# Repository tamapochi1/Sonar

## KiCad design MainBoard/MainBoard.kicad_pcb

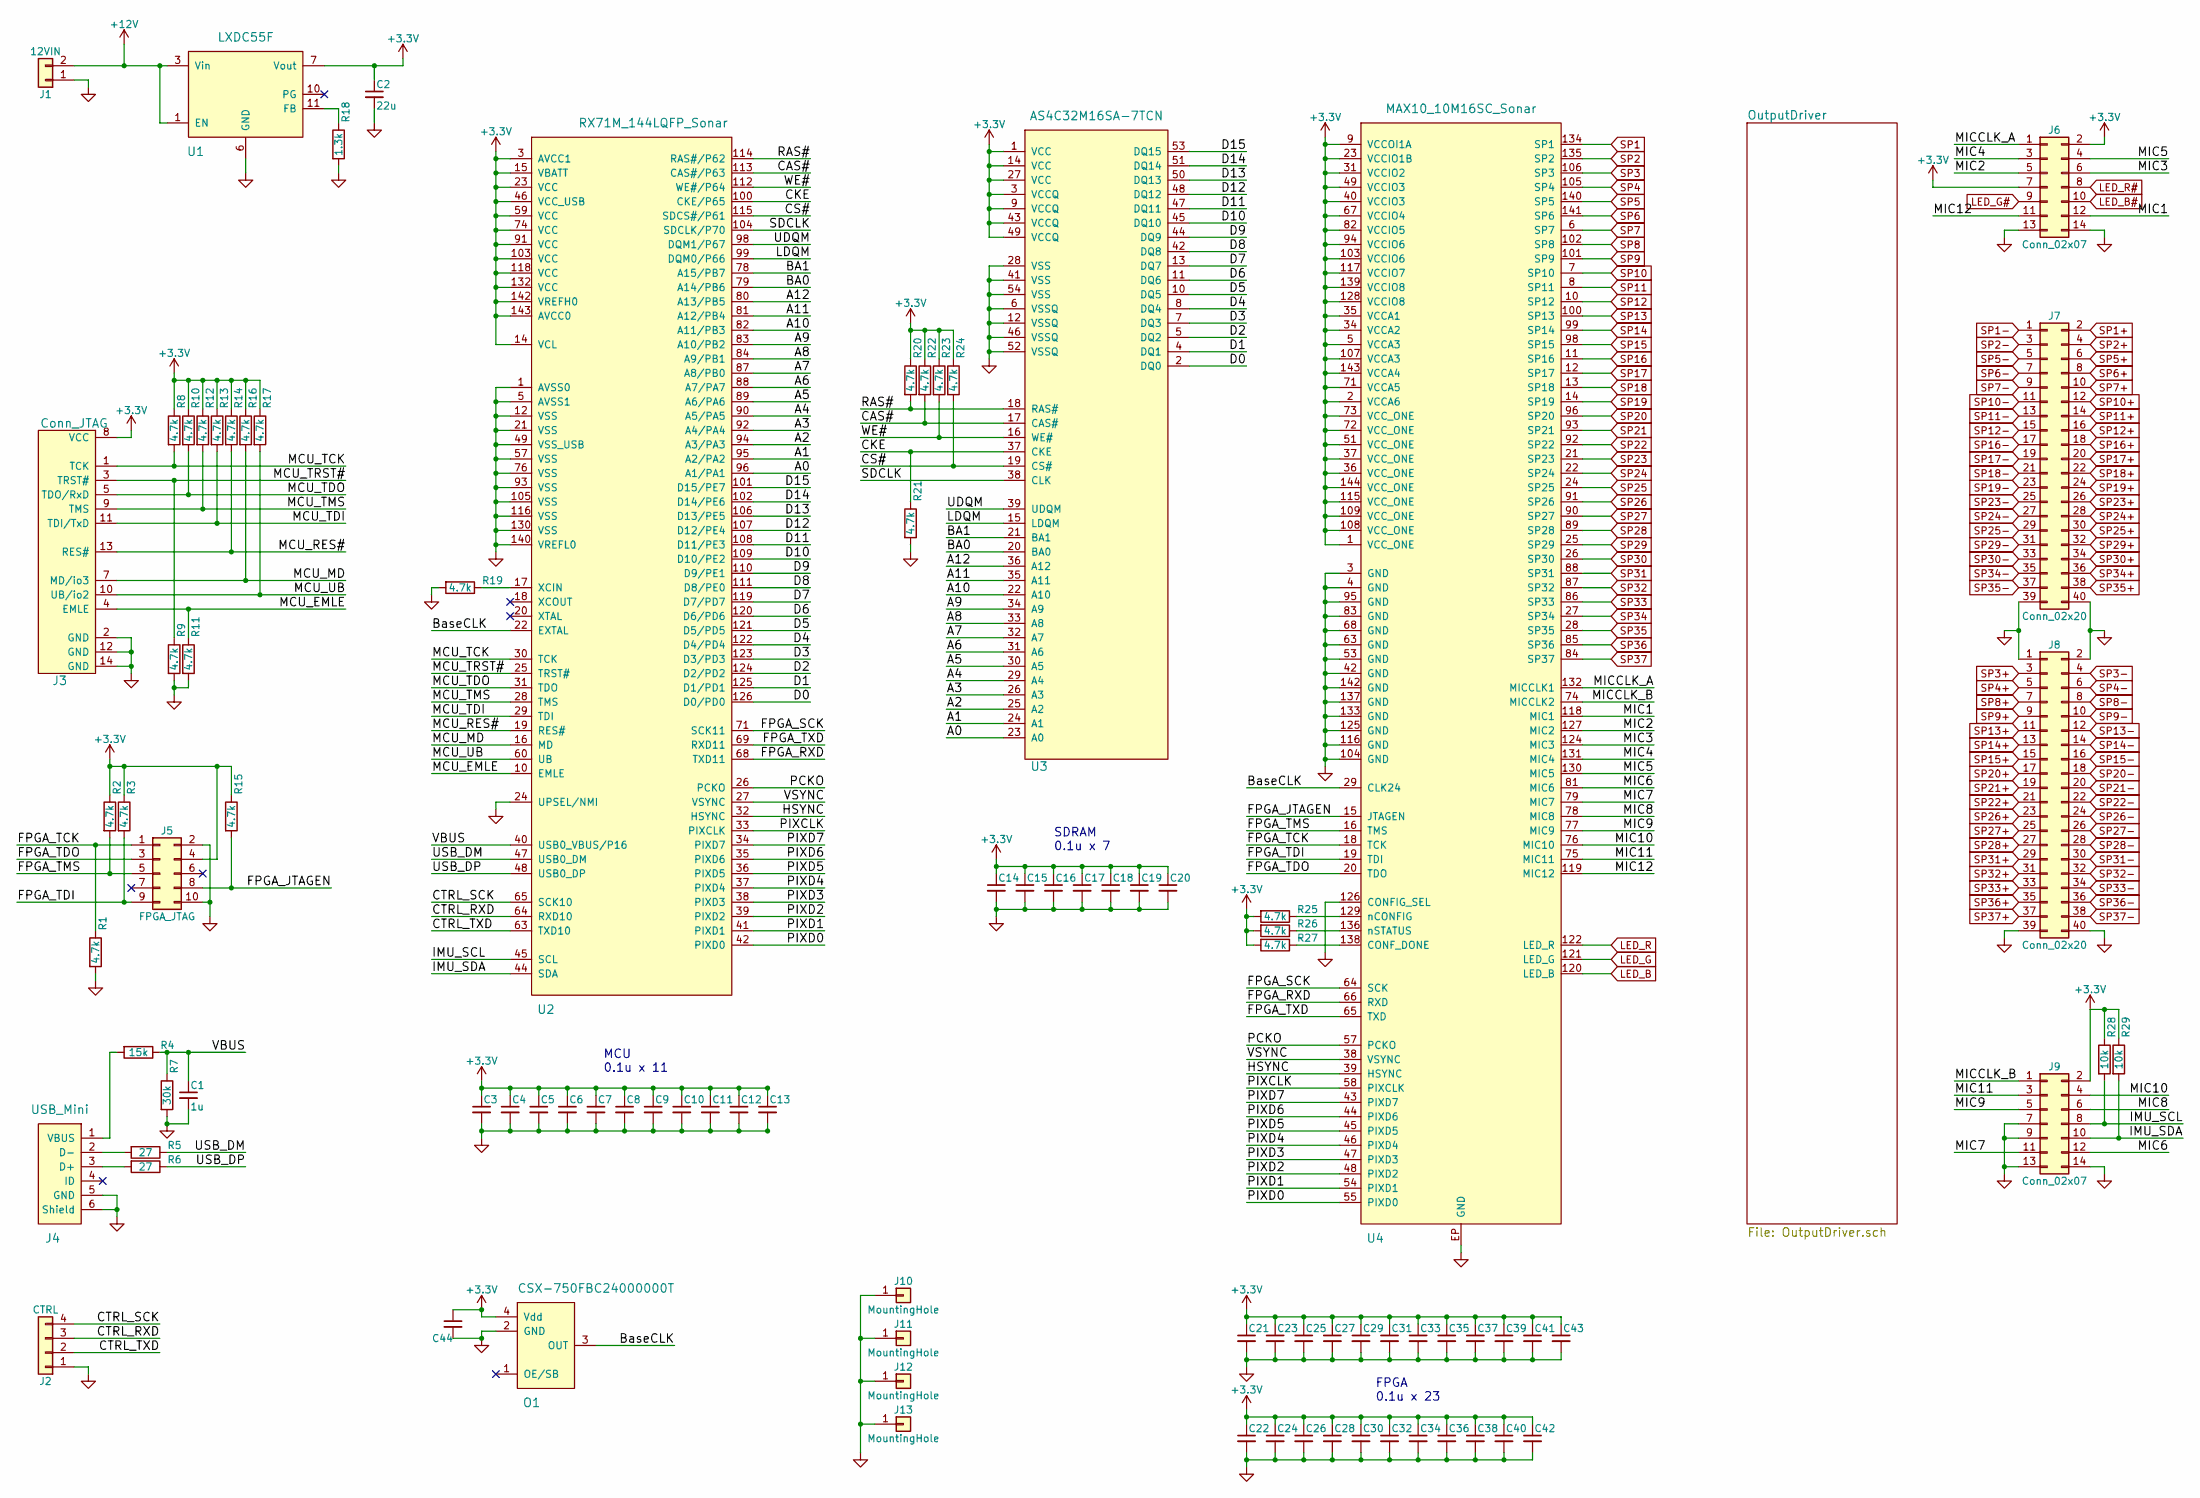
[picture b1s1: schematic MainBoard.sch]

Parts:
C1: 1u; C_0603
C2: 22u; C_1210
C3, C4, C5, C6, C7, C8, C9, C10, C11, C12, C13, C14, C15, C16, C17, C18, C19, C20, C21, C22, C23, C24, C25, C26, C27, C28, C29, C30, C31, C32, C33, C34, C35, C36, C37, C38, C39, C40, C41, C42, C43, C44: 0.1u; C_0402
J1: 12VIN; TerminalBlock_bornier-2_P5.08mm
J2: CTRL; TerminalBlock_bornier-4_P5.08mm
J3: Conn_JTAG; JTAG
J4: USB_Mini; XM7D-0512
J5: FPGA_JTAG; Pin_Header_Angled_2x05_Pitch2.54mm
J6, J9: Conn_02x07; Pin_Header_Straight_2x07_Pitch2.54mm
J7, J8: Conn_02x20; Pin_Header_Straight_2x20_Pitch2.54mm
J10, J11, J12, J13: MountingHole; MountingHole_3.2mm_M3_Pad
O1: CSX-750FBC24000000T; Oscillator_SMD_SeikoEpson_SG8002CA-4pin_7.0x5.0mm
R1, R2, R3, R8, R9, R10, R11, R12, R13, R14, R15, R16, R17, R19, R20, R21, R22, R23, R24, R25, R26, R27: 4.7k; R_0603
R4: 15k; R_0603
R5, R6: 27; R_0603
R7: 30k; R_0603
R18: 1.3k; R_0603
R28, R29: 10k; R_0603
U1: LXDC55F; LXDC55FA
U2: RX71M_144LQFP_Sonar; LQFP-144_20x20mm_Pitch0.5mm
U3: AS4C32M16SA-7TCN; TSOP-II_54
U4: MAX10_10M16SC_Sonar; EQFP-144_A_1.65_D2_4.00

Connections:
+3V3: C2.1, C3.1, C4.1, C5.1, C6.1, C7.1, C8.1, C9.1, C10.1, C11.1, C12.1, C13.1, C14.1, C15.1, C16.1, C17.1, C18.1, C19.1, C20.1, C21.1, C22.1, C23.1, C24.1, C25.1, C26.1, C27.1, C28.1, C29.1, C30.1, C31.1, C32.1, C33.1, C34.1, C35.1, C36.1, C37.1, C38.1, C39.1, C40.1, C41.1, C42.1, C43.1, C44.1, J3.8 (VCC), J5.4, J6.2, J6.7, J9.2, O1.4 (Vdd), R2.1, R3.1, R8.1, R10.1, R12.1, R13.1, R14.1, R15.1, R16.1, R17.1, R20.1, R22.1, R23.1, R24.1, R25.2, R26.2, R27.2, R28.1, R29.1, U1.7 (Vout), U2.3 (AVCC1), U2.14 (VCL), U2.15 (VBATT), U2.23 (VCC), U2.46 (VCC_USB), U2.59 (VCC), U2.74 (VCC), U2.91 (VCC), U2.103 (VCC), U2.118 (VCC), U2.132 (VCC), U2.142 (VREFH0), U2.143 (AVCC0), U3.1 (VCC), U3.3 (VCCQ), U3.9 (VCCQ), U3.14 (VCC), U3.27 (VCC), U3.43 (VCCQ), U3.49 (VCCQ), U4.1 (VCC_ONE), U4.2 (VCCA6), U4.5 (VCCA3), U4.9 (VCCOI1A), U4.23 (VCCIO1B), U4.31 (VCCIO2), U4.34 (VCCA2), U4.35 (VCCA1), U4.36 (VCC_ONE), U4.37 (VCC_ONE), U4.40 (VCCIO3), U4.49 (VCCIO3), U4.51 (VCC_ONE), U4.67 (VCCIO4), U4.71 (VCCA5), U4.72 (VCC_ONE), U4.73 (VCC_ONE), U4.82 (VCCIO5), U4.94 (VCCIO6), U4.103 (VCCIO6), U4.107 (VCCA3), U4.108 (VCC_ONE), U4.109 (VCC_ONE), U4.115 (VCC_ONE), U4.117 (VCCIO7), U4.128 (VCCIO8), U4.139 (VCCIO8), U4.143 (VCCA4), U4.144 (VCC_ONE); also elsewhere on the board
+12V: J1.2, U1.1 (EN), U1.3 (Vin); also elsewhere on the board
/A0: U2.96 (A1/PA1), U3.23 (A0)
/A1: U2.95 (A2/PA2), U3.24 (A1)
/A2: U2.94 (A3/PA3), U3.25 (A2)
/A3: U2.92 (A4/PA4), U3.26 (A3)
/A4: U2.90 (A5/PA5), U3.29 (A4)
/A5: U2.89 (A6/PA6), U3.30 (A5)
/A6: U2.88 (A7/PA7), U3.31 (A6)
/A7: U2.87 (A8/PB0), U3.32 (A7)
/A8: U2.84 (A9/PB1), U3.33 (A8)
/A9: U2.83 (A10/PB2), U3.34 (A9)
/A10: U2.82 (A11/PB3), U3.22 (A10)
/A11: U2.81 (A12/PB4), U3.35 (A11)
/A12: U2.80 (A13/PB5), U3.36 (A12)
/BA0: U2.79 (A14/PB6), U3.20 (BA0)
/BA1: U2.78 (A15/PB7), U3.21 (BA1)
/BaseCLK: O1.3 (OUT), U2.22 (EXTAL), U4.29 (CLK24)
/CAS#: R22.2, U2.113 (CAS#/P63), U3.17 (CAS#)
/CKE: R21.1, U2.100 (CKE/P65), U3.37 (CKE)
/CS#: R24.2, U2.115 (SDCS#/P61), U3.19 (CS#)
/CTRL_RXD: J2.3, U2.64 (RXD10)
/CTRL_SCK: J2.4, U2.65 (SCK10)
/CTRL_TXD: J2.2, U2.63 (TXD10)
/D0: U2.126 (D0/PD0), U3.2 (DQ0)
/D1: U2.125 (D1/PD1), U3.4 (DQ1)
/D2: U2.124 (D2/PD2), U3.5 (DQ2)
/D3: U2.123 (D3/PD3), U3.7 (DQ3)
/D4: U2.122 (D4/PD4), U3.8 (DQ4)
/D5: U2.121 (D5/PD5), U3.10 (DQ5)
/D6: U2.120 (D6/PD6), U3.11 (DQ6)
/D7: U2.119 (D7/PD7), U3.13 (DQ7)
/D8: U2.111 (D8/PE0), U3.42 (DQ8)
/D9: U2.110 (D9/PE1), U3.44 (DQ9)
/D10: U2.109 (D10/PE2), U3.45 (DQ10)
/D11: U2.108 (D11/PE3), U3.47 (DQ11)
/D12: U2.107 (D12/PE4), U3.48 (DQ12)
/D13: U2.106 (D13/PE5), U3.50 (DQ13)
/D14: U2.102 (D14/PE6), U3.51 (DQ14)
/D15: U2.101 (D15/PE7), U3.53 (DQ15)
/FPGA_JTAGEN: J5.8, R15.2, U4.15 (JTAGEN)
/FPGA_RXD: U2.68 (TXD11), U4.66 (RXD)
/FPGA_SCK: U2.71 (SCK11), U4.64 (SCK)
/FPGA_TCK: J5.1, R1.1, U4.18 (TCK)
/FPGA_TDI: J5.9, R3.2, U4.19 (TDI)
/FPGA_TDO: J5.3, U4.20 (TDO)
/FPGA_TMS: J5.5, R2.2, U4.16 (TMS)
/FPGA_TXD: U2.69 (RXD11), U4.65 (TXD)
/HSYNC: U2.32 (HSYNC), U4.39 (HSYNC)
/IMU_SCL: J9.8, R28.2, U2.45 (SCL)
/IMU_SDA: J9.10, R29.2, U2.44 (SDA)
/LDQM: U2.99 (DQM0/P66), U3.15 (LDQM)
/MCU_EMLE: J3.4 (EMLE), R11.1, U2.10 (EMLE)
/MCU_MD: J3.7 (MD/io3), R16.2, U2.16 (MD)
/MCU_RES#: J3.13 (RES#), R14.2, U2.19 (RES#)
/MCU_TCK: J3.1 (TCK), R8.2, U2.30 (TCK)
/MCU_TDI: J3.11 (TDI/TxD), R13.2, U2.29 (TDI)
/MCU_TDO: J3.5 (TDO/RxD), R10.2, U2.31 (TDO)
/MCU_TMS: J3.9 (TMS), R12.2, U2.28 (TMS)
/MCU_TRST#: J3.3 (TRST#), R9.1, U2.25 (TRST#)
/MCU_UB: J3.10 (UB/io2), R17.2, U2.60 (UB)
/MIC1: J6.12, U4.118 (MIC1)
/MIC2: J6.5, U4.127 (MIC2)
/MIC3: J6.6, U4.124 (MIC3)
/MIC4: J6.3, U4.131 (MIC4)
/MIC5: J6.4, U4.130 (MIC5)
/MIC6: J9.12, U4.81 (MIC6)
/MIC7: J9.11, U4.79 (MIC7)
/MIC8: J9.6, U4.78 (MIC8)
/MIC9: J9.5, U4.77 (MIC9)
/MIC10: J9.4, U4.76 (MIC10)
/MIC11: J9.3, U4.75 (MIC11)
/MIC12: J6.11, U4.119 (MIC12)
/MICCLK_A: J6.1, U4.132 (MICCLK1)
/MICCLK_B: J9.1, U4.74 (MICCLK2)
/PCKO: U2.26 (PCKO), U4.57 (PCKO)
/PIXCLK: U2.33 (PIXCLK), U4.58 (PIXCLK)
/PIXD0: U2.42 (PIXD0), U4.55 (PIXD0)
/PIXD1: U2.41 (PIXD1), U4.54 (PIXD1)
/PIXD2: U2.39 (PIXD2), U4.48 (PIXD2)
/PIXD3: U2.38 (PIXD3), U4.47 (PIXD3)
/PIXD4: U2.37 (PIXD4), U4.46 (PIXD4)
/PIXD5: U2.36 (PIXD5), U4.45 (PIXD5)
/PIXD6: U2.35 (PIXD6), U4.44 (PIXD6)
/PIXD7: U2.34 (PIXD7), U4.43 (PIXD7)
/RAS#: R20.2, U2.114 (RAS#/P62), U3.18 (RAS#)
/SDCLK: U2.104 (SDCLK/P70), U3.38 (CLK)
/UDQM: U2.98 (DQM1/P67), U3.39 (UDQM)
/USB_DM: R5.1, U2.47 (USB0_DM)
/USB_DP: R6.1, U2.48 (USB0_DP)
/VBUS: C1.1, R4.1, R7.1, U2.40 (USB0_VBUS/P16)
/VSYNC: U2.27 (VSYNC), U4.38 (VSYNC)
/WE#: R23.2, U2.112 (WE#/P64), U3.16 (WE#)
GND: C1.2, C2.2, C3.2, C4.2, C5.2, C6.2, C7.2, C8.2, C9.2, C10.2, C11.2, C12.2, C13.2, C14.2, C15.2, C16.2, C17.2, C18.2, C19.2, C20.2, C21.2, C22.2, C23.2, C24.2, C25.2, C26.2, C27.2, C28.2, C29.2, C30.2, C31.2, C32.2, C33.2, C34.2, C35.2, C36.2, C37.2, C38.2, C39.2, C40.2, C41.2, C42.2, C43.2, C44.2, J1.1, J2.1, J3.2 (GND), J3.12 (GND), J3.14 (GND), J4.5 (GND), J4.6 (Shield), J5.2, J5.10, J6.13, J6.14, J7.39, J7.40, J8.1, J8.2, J8.39, J8.40, J9.7, J9.9, J9.13, J9.14, J10.1, J11.1, J12.1, J13.1, O1.2 (GND), R1.2, R7.2, R9.2, R11.2, R18.2, R19.2, R21.2, U1.6 (GND), U2.1 (AVSS0), U2.5 (AVSS1), U2.12 (VSS), U2.21 (VSS), U2.24 (UPSEL/NMI), U2.49 (VSS_USB), U2.57 (VSS), U2.76 (VSS), U2.93 (VSS), U2.105 (VSS), U2.116 (VSS), U2.130 (VSS), U2.140 (VREFL0), U3.6 (VSSQ), U3.12 (VSSQ), U3.28 (VSS), U3.41 (VSS), U3.46 (VSSQ), U3.52 (VSSQ), U3.54 (VSS), U4.3 (GND), U4.4 (GND), U4.42 (GND), U4.53 (GND), U4.63 (GND), U4.68 (GND), U4.83 (GND), U4.95 (GND), U4.104 (GND), U4.116 (GND), U4.125 (GND), U4.126 (CONFIG_SEL), U4.133 (GND), U4.137 (GND), U4.142 (GND), U4.EP (GND); also elsewhere on the board
LED_B: U4.120 (LED_B); also elsewhere on the board
LED_B#: J6.10; also elsewhere on the board
LED_G: U4.121 (LED_G); also elsewhere on the board
LED_G#: J6.9; also elsewhere on the board
LED_R: U4.122 (LED_R); also elsewhere on the board
LED_R#: J6.8; also elsewhere on the board
unnamed: J4.1 (VBUS), R4.2
unnamed: J4.2 (D-), R5.2
unnamed: J4.3 (D+), R6.2
unnamed: R18.1, U1.11 (FB)
unnamed: R19.1, U2.17 (XCIN)
unnamed: R25.1, U4.129 (nCONFIG)
unnamed: R26.1, U4.136 (nSTATUS)
unnamed: R27.1, U4.138 (CONF_DONE)
SP1: U4.134 (SP1); also elsewhere on the board
SP1+: J7.2; also elsewhere on the board
SP1-: J7.1; also elsewhere on the board
SP2: U4.135 (SP2); also elsewhere on the board
SP2+: J7.4; also elsewhere on the board
SP2-: J7.3; also elsewhere on the board
SP3: U4.106 (SP3); also elsewhere on the board
SP3+: J8.3; also elsewhere on the board
SP3-: J8.4; also elsewhere on the board
SP4: U4.105 (SP4); also elsewhere on the board
SP4+: J8.5; also elsewhere on the board
SP4-: J8.6; also elsewhere on the board
SP5: U4.140 (SP5); also elsewhere on the board
SP5+: J7.6; also elsewhere on the board
SP5-: J7.5; also elsewhere on the board
SP6: U4.141 (SP6); also elsewhere on the board
SP6+: J7.8; also elsewhere on the board
SP6-: J7.7; also elsewhere on the board
SP7: U4.6 (SP7); also elsewhere on the board
SP7+: J7.10; also elsewhere on the board
SP7-: J7.9; also elsewhere on the board
SP8: U4.102 (SP8); also elsewhere on the board
SP8+: J8.7; also elsewhere on the board
SP8-: J8.8; also elsewhere on the board
SP9: U4.101 (SP9); also elsewhere on the board
SP9+: J8.9; also elsewhere on the board
SP9-: J8.10; also elsewhere on the board
SP10: U4.7 (SP10); also elsewhere on the board
SP10+: J7.12; also elsewhere on the board
SP10-: J7.11; also elsewhere on the board
SP11: U4.8 (SP11); also elsewhere on the board
SP11+: J7.14; also elsewhere on the board
SP11-: J7.13; also elsewhere on the board
SP12: U4.10 (SP12); also elsewhere on the board
SP12+: J7.16; also elsewhere on the board
SP12-: J7.15; also elsewhere on the board
SP13: U4.100 (SP13); also elsewhere on the board
SP13+: J8.11; also elsewhere on the board
SP13-: J8.12; also elsewhere on the board
SP14: U4.99 (SP14); also elsewhere on the board
SP14+: J8.13; also elsewhere on the board
SP14-: J8.14; also elsewhere on the board
SP15: U4.98 (SP15); also elsewhere on the board
SP15+: J8.15; also elsewhere on the board
SP15-: J8.16; also elsewhere on the board
SP16: U4.11 (SP16); also elsewhere on the board
SP16+: J7.18; also elsewhere on the board
SP16-: J7.17; also elsewhere on the board
SP17: U4.12 (SP17); also elsewhere on the board
SP17+: J7.20; also elsewhere on the board
SP17-: J7.19; also elsewhere on the board
SP18: U4.13 (SP18); also elsewhere on the board
SP18+: J7.22; also elsewhere on the board
SP18-: J7.21; also elsewhere on the board
SP19: U4.14 (SP19); also elsewhere on the board
SP19+: J7.24; also elsewhere on the board
SP19-: J7.23; also elsewhere on the board
SP20: U4.96 (SP20); also elsewhere on the board
SP20+: J8.17; also elsewhere on the board
SP20-: J8.18; also elsewhere on the board
SP21: U4.93 (SP21); also elsewhere on the board
SP21+: J8.19; also elsewhere on the board
SP21-: J8.20; also elsewhere on the board
SP22: U4.92 (SP22); also elsewhere on the board
SP22+: J8.21; also elsewhere on the board
SP22-: J8.22; also elsewhere on the board
SP23: U4.21 (SP23); also elsewhere on the board
SP23+: J7.26; also elsewhere on the board
SP23-: J7.25; also elsewhere on the board
SP24: U4.22 (SP24); also elsewhere on the board
SP24+: J7.28; also elsewhere on the board
SP24-: J7.27; also elsewhere on the board
SP25: U4.24 (SP25); also elsewhere on the board
SP25+: J7.30; also elsewhere on the board
SP25-: J7.29; also elsewhere on the board
SP26: U4.91 (SP26); also elsewhere on the board
SP26+: J8.23; also elsewhere on the board
SP26-: J8.24; also elsewhere on the board
SP27: U4.90 (SP27); also elsewhere on the board
SP27+: J8.25; also elsewhere on the board
SP27-: J8.26; also elsewhere on the board
SP28: U4.89 (SP28); also elsewhere on the board
SP28+: J8.27; also elsewhere on the board
SP28-: J8.28; also elsewhere on the board
SP29: U4.25 (SP29); also elsewhere on the board
SP29+: J7.32; also elsewhere on the board
SP29-: J7.31; also elsewhere on the board
SP30: U4.26 (SP30); also elsewhere on the board
SP30+: J7.34; also elsewhere on the board
SP30-: J7.33; also elsewhere on the board
SP31: U4.88 (SP31); also elsewhere on the board
SP31+: J8.29; also elsewhere on the board
SP31-: J8.30; also elsewhere on the board
SP32: U4.87 (SP32); also elsewhere on the board
SP32+: J8.31; also elsewhere on the board
SP32-: J8.32; also elsewhere on the board
SP33: U4.86 (SP33); also elsewhere on the board
SP33+: J8.33; also elsewhere on the board
SP33-: J8.34; also elsewhere on the board
SP34: U4.27 (SP34); also elsewhere on the board
SP34+: J7.36; also elsewhere on the board
SP34-: J7.35; also elsewhere on the board
SP35: U4.28 (SP35); also elsewhere on the board
SP35+: J7.38; also elsewhere on the board
SP35-: J7.37; also elsewhere on the board
SP36: U4.85 (SP36); also elsewhere on the board
SP36+: J8.35; also elsewhere on the board
SP36-: J8.36; also elsewhere on the board
SP37: U4.84 (SP37); also elsewhere on the board
SP37+: J8.37; also elsewhere on the board
SP37-: J8.38; also elsewhere on the board

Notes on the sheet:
FPGA 0.1u x 23
SDRAM 0.1u x 7
MCU 0.1u x 11

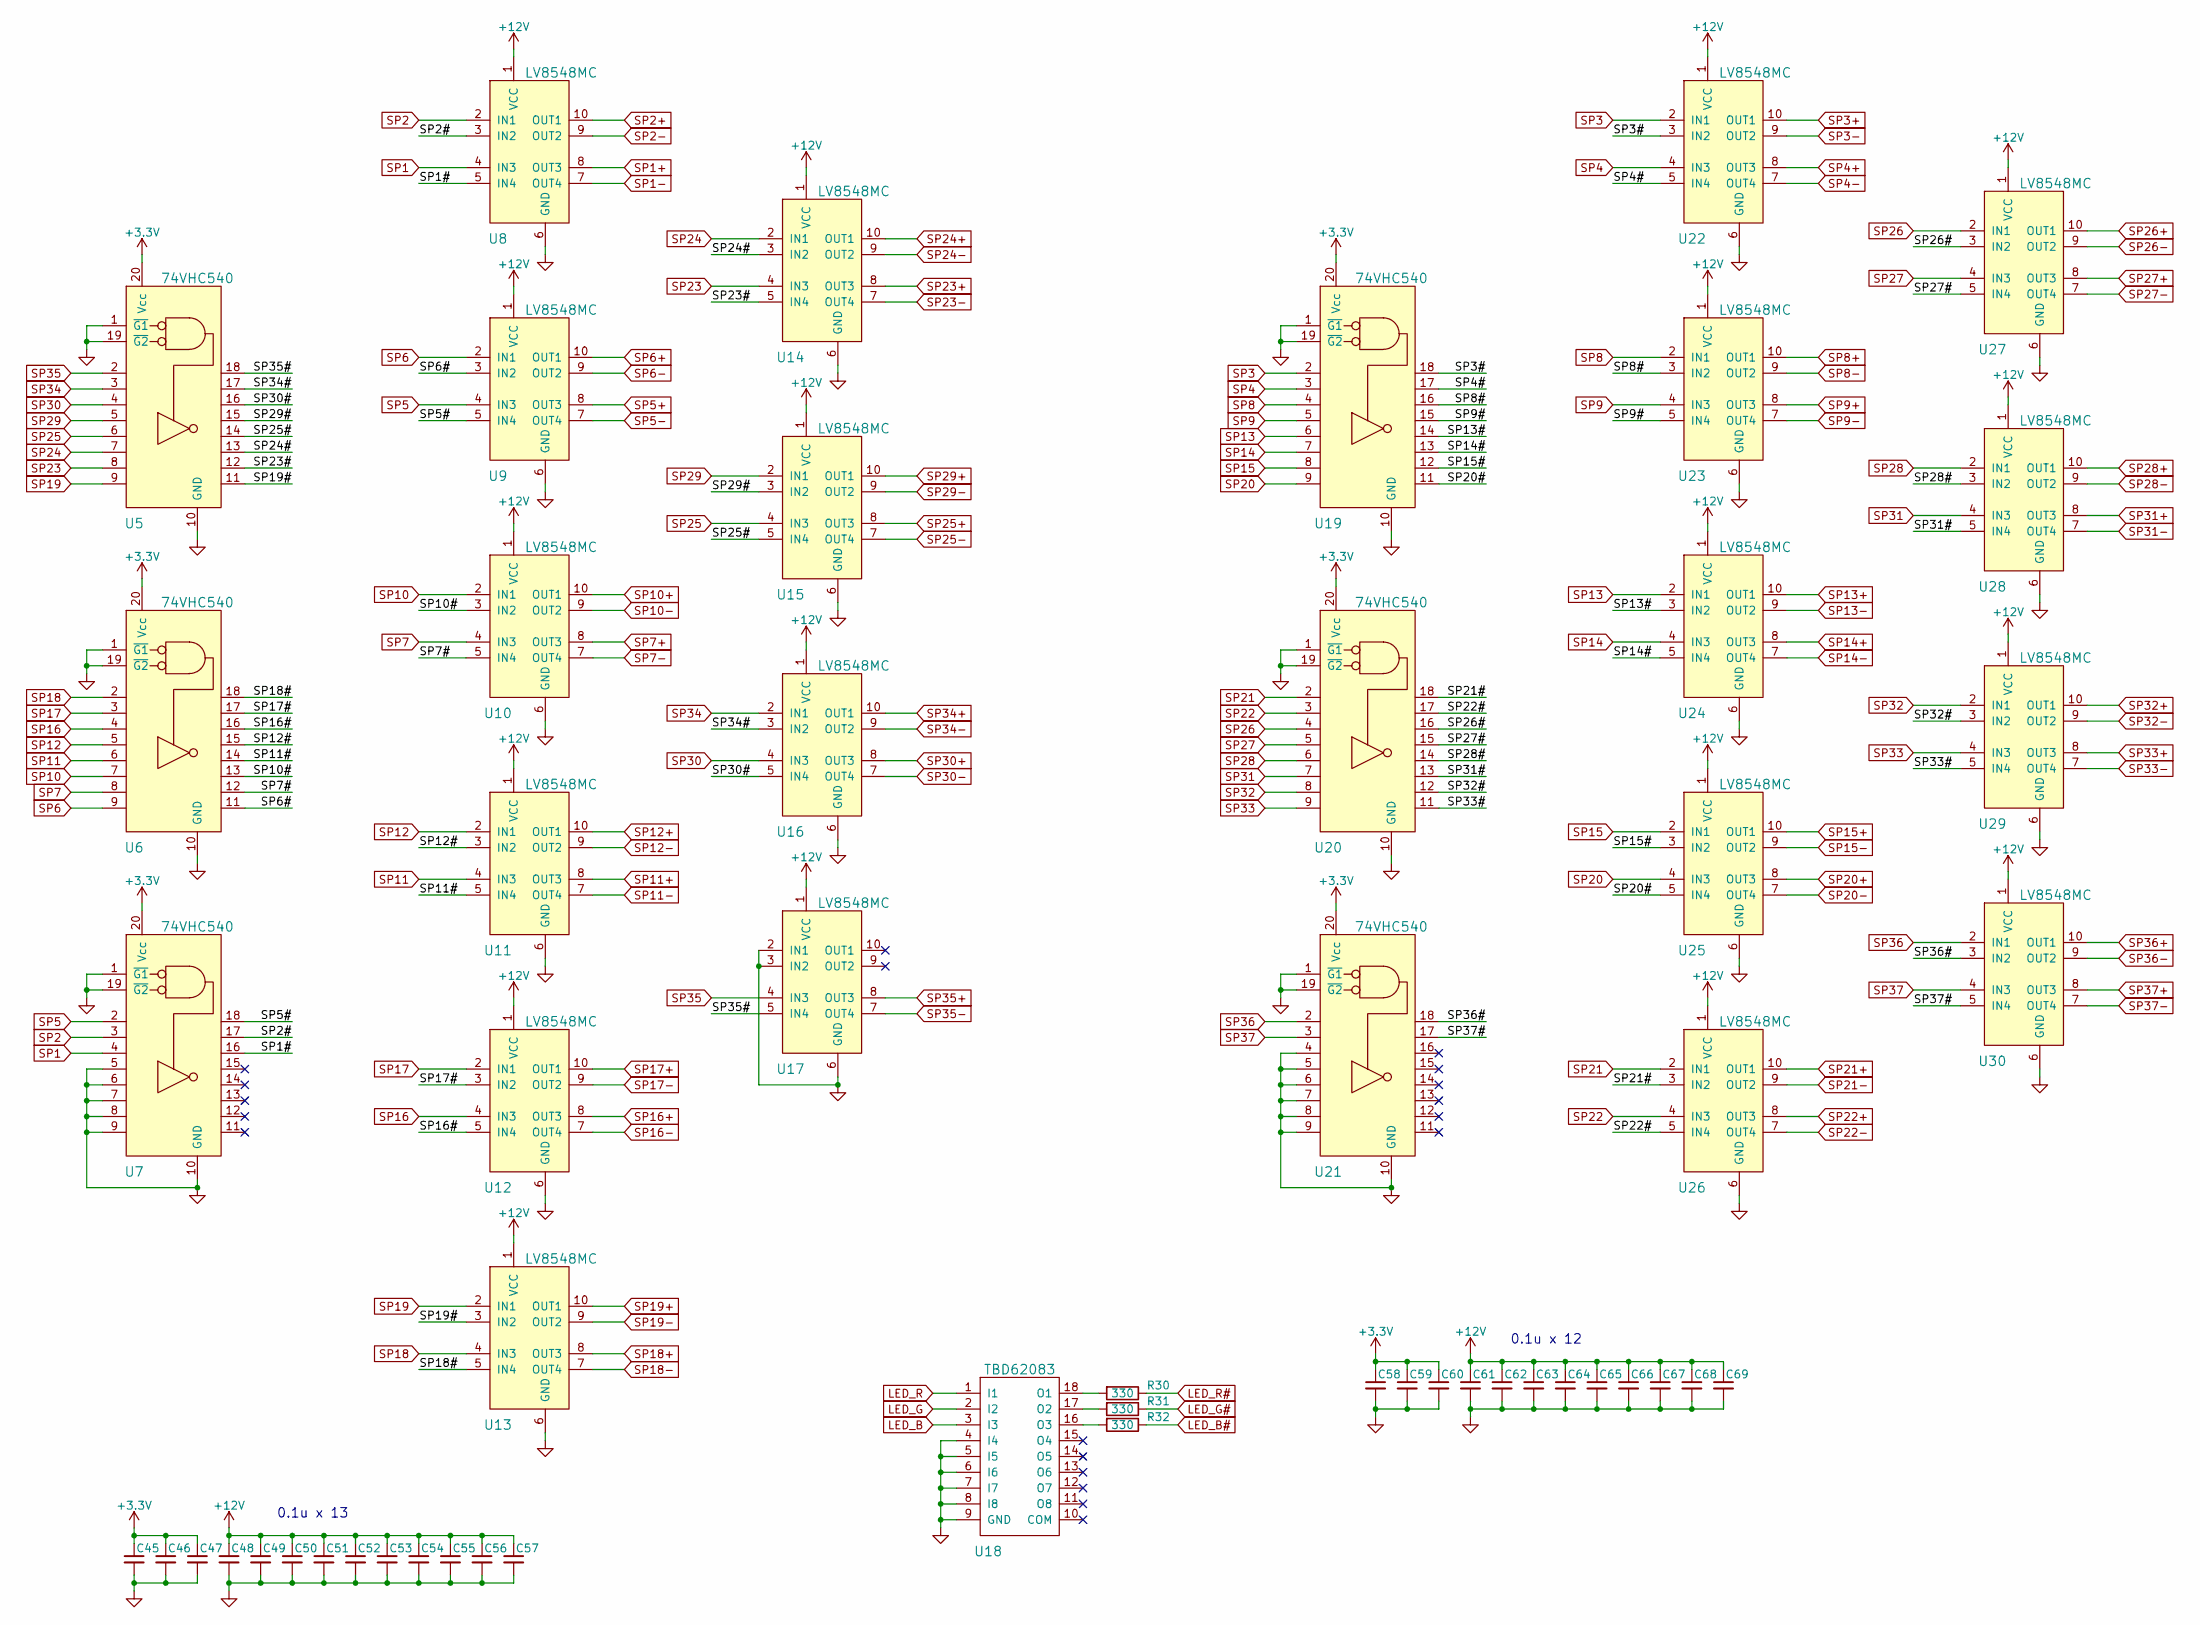
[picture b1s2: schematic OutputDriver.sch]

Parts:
C45, C46, C47, C48, C49, C50, C51, C52, C53, C54, C55, C56, C57, C58, C59, C60, C61, C62, C63, C64, C65, C66, C67, C68, C69: 0.1u; C_0402
R30, R31, R32: 330; R_0603
U5, U6, U7, U19, U20, U21: 74VHC540; TSSOP-20_4.4x6.5mm_Pitch0.65mm
U8, U9, U10, U11, U12, U13, U14, U15, U16, U17, U22, U23, U24, U25, U26, U27, U28, U29, U30: LV8548MC; SOIC10_R
U18: TBD62083; SSOP18_R

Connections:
+3V3: C45.1, C46.1, C47.1, C58.1, C59.1, C60.1, U5.20 (Vcc), U6.20 (Vcc), U7.20 (Vcc), U19.20 (Vcc), U20.20 (Vcc), U21.20 (Vcc); also elsewhere on the board
+12V: C48.1, C49.1, C50.1, C51.1, C52.1, C53.1, C54.1, C55.1, C56.1, C57.1, C61.1, C62.1, C63.1, C64.1, C65.1, C66.1, C67.1, C68.1, C69.1, U8.1 (VCC), U9.1 (VCC), U10.1 (VCC), U11.1 (VCC), U12.1 (VCC), U13.1 (VCC), U14.1 (VCC), U15.1 (VCC), U16.1 (VCC), U17.1 (VCC), U22.1 (VCC), U23.1 (VCC), U24.1 (VCC), U25.1 (VCC), U26.1 (VCC), U27.1 (VCC), U28.1 (VCC), U29.1 (VCC), U30.1 (VCC); also elsewhere on the board
/OutputDriver/SP1#: U7.16, U8.5 (IN4)
/OutputDriver/SP2#: U7.17, U8.3 (IN2)
/OutputDriver/SP3#: U19.18, U22.3 (IN2)
/OutputDriver/SP4#: U19.17, U22.5 (IN4)
/OutputDriver/SP5#: U7.18, U9.5 (IN4)
/OutputDriver/SP6#: U6.11, U9.3 (IN2)
/OutputDriver/SP7#: U6.12, U10.5 (IN4)
/OutputDriver/SP8#: U19.16, U23.3 (IN2)
/OutputDriver/SP9#: U19.15, U23.5 (IN4)
/OutputDriver/SP10#: U6.13, U10.3 (IN2)
/OutputDriver/SP11#: U6.14, U11.5 (IN4)
/OutputDriver/SP12#: U6.15, U11.3 (IN2)
/OutputDriver/SP13#: U19.14, U24.3 (IN2)
/OutputDriver/SP14#: U19.13, U24.5 (IN4)
/OutputDriver/SP15#: U19.12, U25.3 (IN2)
/OutputDriver/SP16#: U6.16, U12.5 (IN4)
/OutputDriver/SP17#: U6.17, U12.3 (IN2)
/OutputDriver/SP18#: U6.18, U13.5 (IN4)
/OutputDriver/SP19#: U5.11, U13.3 (IN2)
/OutputDriver/SP20#: U19.11, U25.5 (IN4)
/OutputDriver/SP21#: U20.18, U26.3 (IN2)
/OutputDriver/SP22#: U20.17, U26.5 (IN4)
/OutputDriver/SP23#: U5.12, U14.5 (IN4)
/OutputDriver/SP24#: U5.13, U14.3 (IN2)
/OutputDriver/SP25#: U5.14, U15.5 (IN4)
/OutputDriver/SP26#: U20.16, U27.3 (IN2)
/OutputDriver/SP27#: U20.15, U27.5 (IN4)
/OutputDriver/SP28#: U20.14, U28.3 (IN2)
/OutputDriver/SP29#: U5.15, U15.3 (IN2)
/OutputDriver/SP30#: U5.16, U16.5 (IN4)
/OutputDriver/SP31#: U20.13, U28.5 (IN4)
/OutputDriver/SP32#: U20.12, U29.3 (IN2)
/OutputDriver/SP33#: U20.11, U29.5 (IN4)
/OutputDriver/SP34#: U5.17, U16.3 (IN2)
/OutputDriver/SP35#: U5.18, U17.5 (IN4)
/OutputDriver/SP36#: U21.18, U30.3 (IN2)
/OutputDriver/SP37#: U21.17, U30.5 (IN4)
GND: C45.2, C46.2, C47.2, C48.2, C49.2, C50.2, C51.2, C52.2, C53.2, C54.2, C55.2, C56.2, C57.2, C58.2, C59.2, C60.2, C61.2, C62.2, C63.2, C64.2, C65.2, C66.2, C67.2, C68.2, C69.2, U5.1 (~G1), U5.10 (GND), U5.19 (~G2), U6.1 (~G1), U6.10 (GND), U6.19 (~G2), U7.1 (~G1), U7.5, U7.6, U7.7, U7.8, U7.9, U7.10 (GND), U7.19 (~G2), U8.6 (GND), U9.6 (GND), U10.6 (GND), U11.6 (GND), U12.6 (GND), U13.6 (GND), U14.6 (GND), U15.6 (GND), U16.6 (GND), U17.2 (IN1), U17.3 (IN2), U17.6 (GND), U18.4 (I4), U18.5 (I5), U18.6 (I6), U18.7 (I7), U18.8 (I8), U18.9 (GND), U19.1 (~G1), U19.10 (GND), U19.19 (~G2), U20.1 (~G1), U20.10 (GND), U20.19 (~G2), U21.1 (~G1), U21.4, U21.5, U21.6, U21.7, U21.8, U21.9, U21.10 (GND), U21.19 (~G2), U22.6 (GND), U23.6 (GND), U24.6 (GND), U25.6 (GND), U26.6 (GND), U27.6 (GND), U28.6 (GND), U29.6 (GND), U30.6 (GND); also elsewhere on the board
LED_B: U18.3 (I3); also elsewhere on the board
LED_B#: R32.1; also elsewhere on the board
LED_G: U18.2 (I2); also elsewhere on the board
LED_G#: R31.1; also elsewhere on the board
LED_R: U18.1 (I1); also elsewhere on the board
LED_R#: R30.1; also elsewhere on the board
unnamed: R30.2, U18.18 (O1)
unnamed: R31.2, U18.17 (O2)
unnamed: R32.2, U18.16 (O3)
SP1: U7.4, U8.4 (IN3); also elsewhere on the board
SP1+: U8.8 (OUT3); also elsewhere on the board
SP1-: U8.7 (OUT4); also elsewhere on the board
SP2: U7.3, U8.2 (IN1); also elsewhere on the board
SP2+: U8.10 (OUT1); also elsewhere on the board
SP2-: U8.9 (OUT2); also elsewhere on the board
SP3: U19.2, U22.2 (IN1); also elsewhere on the board
SP3+: U22.10 (OUT1); also elsewhere on the board
SP3-: U22.9 (OUT2); also elsewhere on the board
SP4: U19.3, U22.4 (IN3); also elsewhere on the board
SP4+: U22.8 (OUT3); also elsewhere on the board
SP4-: U22.7 (OUT4); also elsewhere on the board
SP5: U7.2, U9.4 (IN3); also elsewhere on the board
SP5+: U9.8 (OUT3); also elsewhere on the board
SP5-: U9.7 (OUT4); also elsewhere on the board
SP6: U6.9, U9.2 (IN1); also elsewhere on the board
SP6+: U9.10 (OUT1); also elsewhere on the board
SP6-: U9.9 (OUT2); also elsewhere on the board
SP7: U6.8, U10.4 (IN3); also elsewhere on the board
SP7+: U10.8 (OUT3); also elsewhere on the board
SP7-: U10.7 (OUT4); also elsewhere on the board
SP8: U19.4, U23.2 (IN1); also elsewhere on the board
SP8+: U23.10 (OUT1); also elsewhere on the board
SP8-: U23.9 (OUT2); also elsewhere on the board
SP9: U19.5, U23.4 (IN3); also elsewhere on the board
SP9+: U23.8 (OUT3); also elsewhere on the board
SP9-: U23.7 (OUT4); also elsewhere on the board
SP10: U6.7, U10.2 (IN1); also elsewhere on the board
SP10+: U10.10 (OUT1); also elsewhere on the board
SP10-: U10.9 (OUT2); also elsewhere on the board
SP11: U6.6, U11.4 (IN3); also elsewhere on the board
SP11+: U11.8 (OUT3); also elsewhere on the board
SP11-: U11.7 (OUT4); also elsewhere on the board
SP12: U6.5, U11.2 (IN1); also elsewhere on the board
SP12+: U11.10 (OUT1); also elsewhere on the board
SP12-: U11.9 (OUT2); also elsewhere on the board
SP13: U19.6, U24.2 (IN1); also elsewhere on the board
SP13+: U24.10 (OUT1); also elsewhere on the board
SP13-: U24.9 (OUT2); also elsewhere on the board
SP14: U19.7, U24.4 (IN3); also elsewhere on the board
SP14+: U24.8 (OUT3); also elsewhere on the board
SP14-: U24.7 (OUT4); also elsewhere on the board
SP15: U19.8, U25.2 (IN1); also elsewhere on the board
SP15+: U25.10 (OUT1); also elsewhere on the board
SP15-: U25.9 (OUT2); also elsewhere on the board
SP16: U6.4, U12.4 (IN3); also elsewhere on the board
SP16+: U12.8 (OUT3); also elsewhere on the board
SP16-: U12.7 (OUT4); also elsewhere on the board
SP17: U6.3, U12.2 (IN1); also elsewhere on the board
SP17+: U12.10 (OUT1); also elsewhere on the board
SP17-: U12.9 (OUT2); also elsewhere on the board
SP18: U6.2, U13.4 (IN3); also elsewhere on the board
SP18+: U13.8 (OUT3); also elsewhere on the board
SP18-: U13.7 (OUT4); also elsewhere on the board
SP19: U5.9, U13.2 (IN1); also elsewhere on the board
SP19+: U13.10 (OUT1); also elsewhere on the board
SP19-: U13.9 (OUT2); also elsewhere on the board
SP20: U19.9, U25.4 (IN3); also elsewhere on the board
SP20+: U25.8 (OUT3); also elsewhere on the board
SP20-: U25.7 (OUT4); also elsewhere on the board
SP21: U20.2, U26.2 (IN1); also elsewhere on the board
SP21+: U26.10 (OUT1); also elsewhere on the board
SP21-: U26.9 (OUT2); also elsewhere on the board
SP22: U20.3, U26.4 (IN3); also elsewhere on the board
SP22+: U26.8 (OUT3); also elsewhere on the board
SP22-: U26.7 (OUT4); also elsewhere on the board
SP23: U5.8, U14.4 (IN3); also elsewhere on the board
SP23+: U14.8 (OUT3); also elsewhere on the board
SP23-: U14.7 (OUT4); also elsewhere on the board
SP24: U5.7, U14.2 (IN1); also elsewhere on the board
SP24+: U14.10 (OUT1); also elsewhere on the board
SP24-: U14.9 (OUT2); also elsewhere on the board
SP25: U5.6, U15.4 (IN3); also elsewhere on the board
SP25+: U15.8 (OUT3); also elsewhere on the board
SP25-: U15.7 (OUT4); also elsewhere on the board
SP26: U20.4, U27.2 (IN1); also elsewhere on the board
SP26+: U27.10 (OUT1); also elsewhere on the board
SP26-: U27.9 (OUT2); also elsewhere on the board
SP27: U20.5, U27.4 (IN3); also elsewhere on the board
SP27+: U27.8 (OUT3); also elsewhere on the board
SP27-: U27.7 (OUT4); also elsewhere on the board
SP28: U20.6, U28.2 (IN1); also elsewhere on the board
SP28+: U28.10 (OUT1); also elsewhere on the board
SP28-: U28.9 (OUT2); also elsewhere on the board
SP29: U5.5, U15.2 (IN1); also elsewhere on the board
SP29+: U15.10 (OUT1); also elsewhere on the board
SP29-: U15.9 (OUT2); also elsewhere on the board
SP30: U5.4, U16.4 (IN3); also elsewhere on the board
SP30+: U16.8 (OUT3); also elsewhere on the board
SP30-: U16.7 (OUT4); also elsewhere on the board
SP31: U20.7, U28.4 (IN3); also elsewhere on the board
SP31+: U28.8 (OUT3); also elsewhere on the board
SP31-: U28.7 (OUT4); also elsewhere on the board
SP32: U20.8, U29.2 (IN1); also elsewhere on the board
SP32+: U29.10 (OUT1); also elsewhere on the board
SP32-: U29.9 (OUT2); also elsewhere on the board
SP33: U20.9, U29.4 (IN3); also elsewhere on the board
SP33+: U29.8 (OUT3); also elsewhere on the board
SP33-: U29.7 (OUT4); also elsewhere on the board
SP34: U5.3, U16.2 (IN1); also elsewhere on the board
SP34+: U16.10 (OUT1); also elsewhere on the board
SP34-: U16.9 (OUT2); also elsewhere on the board
SP35: U5.2, U17.4 (IN3); also elsewhere on the board
SP35+: U17.8 (OUT3); also elsewhere on the board
SP35-: U17.7 (OUT4); also elsewhere on the board
SP36: U21.2, U30.2 (IN1); also elsewhere on the board
SP36+: U30.10 (OUT1); also elsewhere on the board
SP36-: U30.9 (OUT2); also elsewhere on the board
SP37: U21.3, U30.4 (IN3); also elsewhere on the board
SP37+: U30.8 (OUT3); also elsewhere on the board
SP37-: U30.7 (OUT4); also elsewhere on the board

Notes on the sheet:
0.1u x 13
0.1u x 12

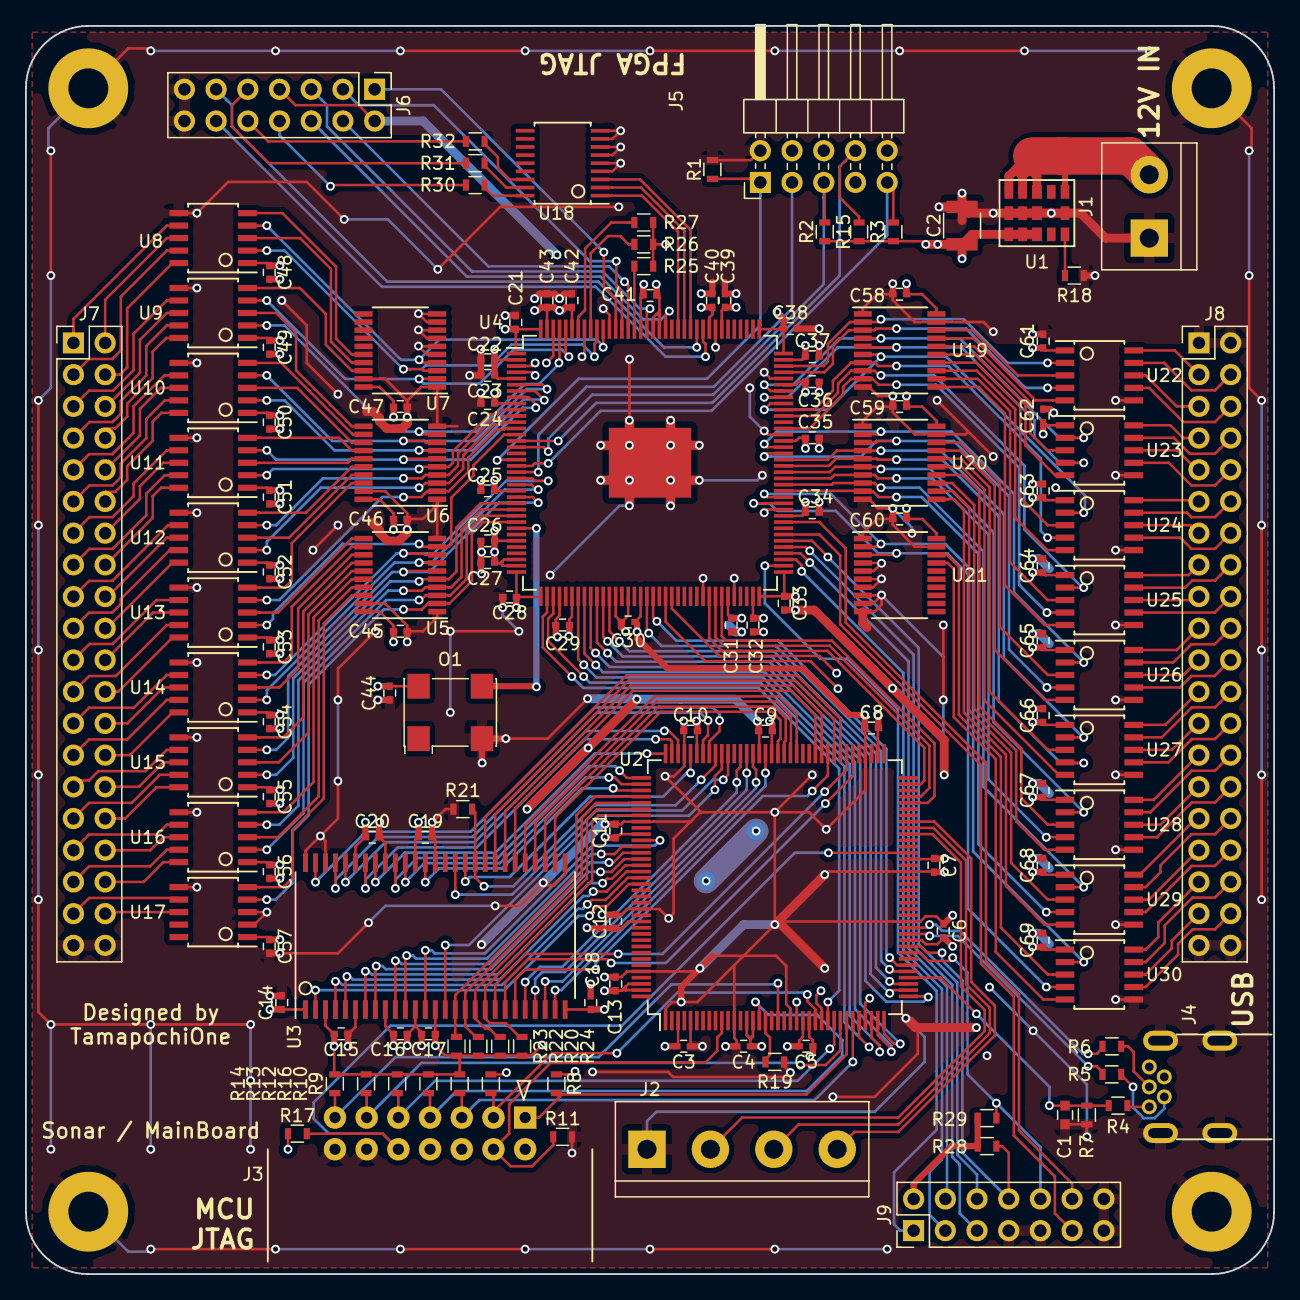
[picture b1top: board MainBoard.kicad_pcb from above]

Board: 4 copper layers, 100.0 x 100.0 mm, 145 parts (0 on the bottom side), 259 nets.
